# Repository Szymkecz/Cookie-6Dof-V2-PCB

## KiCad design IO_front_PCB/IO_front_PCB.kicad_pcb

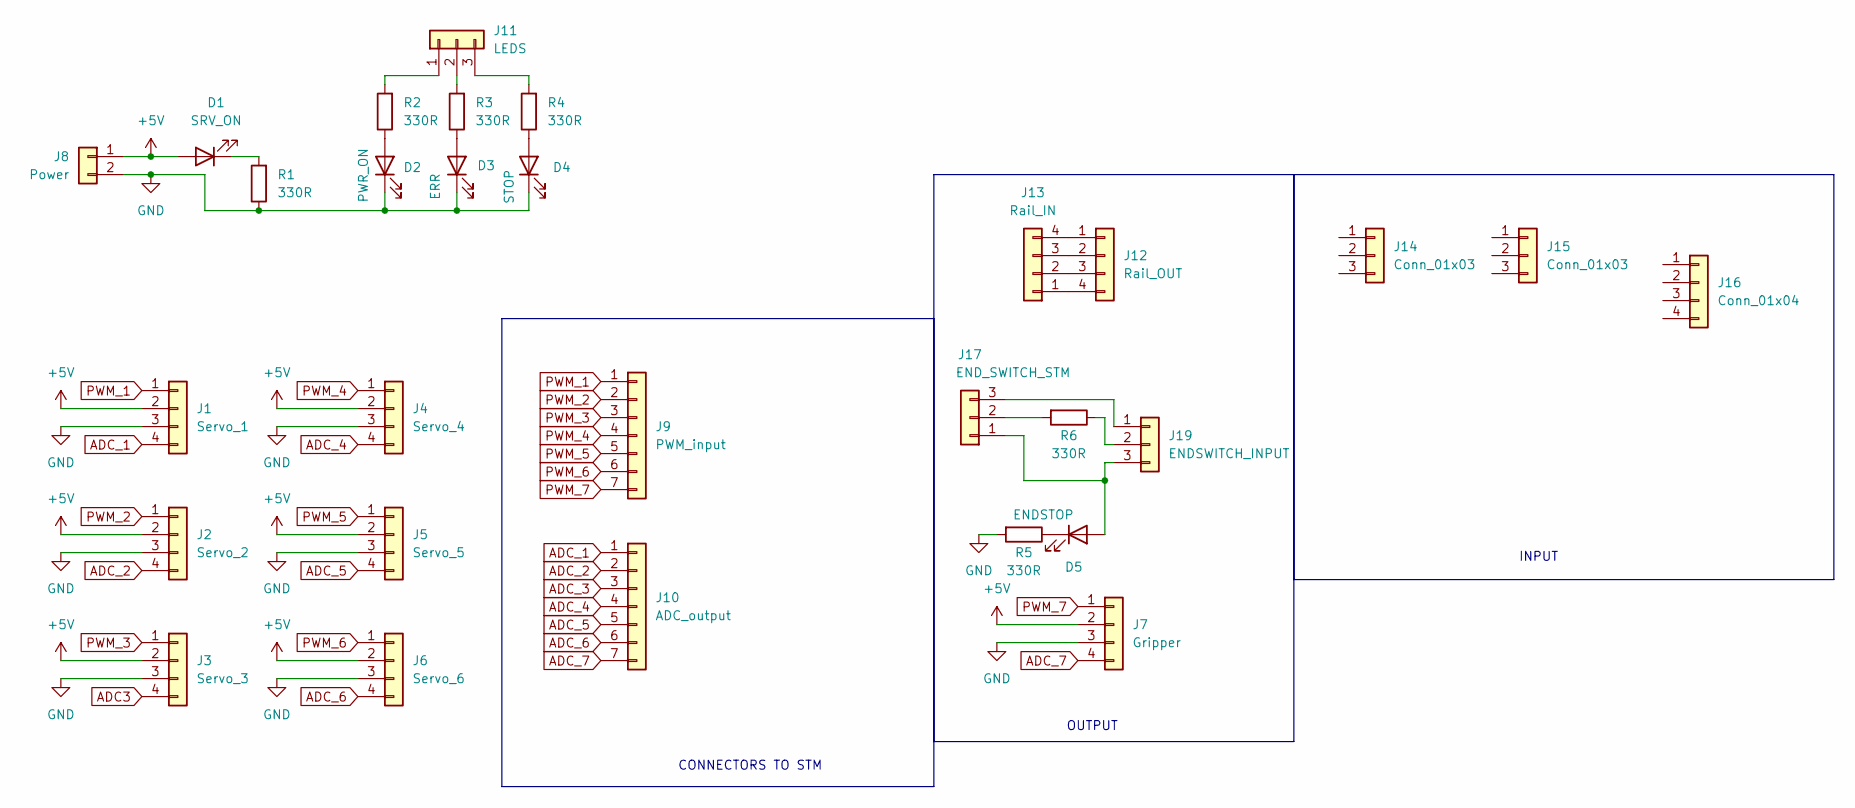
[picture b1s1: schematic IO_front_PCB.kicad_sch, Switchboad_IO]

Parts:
D1: SRV_ON; LED_D3.0mm
D2: PWR_ON; LED_D3.0mm
D3: ERR; LED_D3.0mm
D4: STOP; LED_D3.0mm
D5: ENDSTOP; LED_D3.0mm
J1: Servo_1; JST_XH_B4B-XH-A_1x04_P2.50mm_Vertical
J2: Servo_2; JST_XH_B4B-XH-A_1x04_P2.50mm_Vertical
J3: Servo_3; JST_XH_B4B-XH-A_1x04_P2.50mm_Vertical
J4: Servo_4; JST_XH_B4B-XH-A_1x04_P2.50mm_Vertical
J5: Servo_5; JST_XH_B4B-XH-A_1x04_P2.50mm_Vertical
J6: Servo_6; JST_XH_B4B-XH-A_1x04_P2.50mm_Vertical
J7: Gripper; JST_XH_B4B-XH-A_1x04_P2.50mm_Vertical
J8: Power; TerminalBlock_MaiXu_MX126-5.0-02P_1x02_P5.00mm
J9: PWM_input; PinHeader_1x07_P2.54mm_Vertical
J10: ADC_output; PinHeader_1x07_P2.54mm_Vertical
J11: LEDS; PinHeader_1x03_P2.54mm_Vertical
J12: Rail_OUT; JST_XH_B4B-XH-A_1x04_P2.50mm_Vertical
J13: Rail_IN; JST_XH_B4B-XH-A_1x04_P2.50mm_Vertical
J14, J15: Conn_01x03; JST_XH_B3B-XH-A_1x03_P2.50mm_Vertical
J16: Conn_01x04; JST_XH_B4B-XH-A_1x04_P2.50mm_Vertical
J17: END_SWITCH_STM; PinHeader_1x03_P2.54mm_Vertical
J19: ENDSWITCH_INPUT; JST_XH_B3B-XH-A_1x03_P2.50mm_Vertical
R1, R2, R3, R4, R5, R6: 330R; R_Axial_DIN0207_L6.3mm_D2.5mm_P7.62mm_Horizontal

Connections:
+5V: D1.2 (A), J1.2, J2.2, J3.2, J4.2, J5.2, J6.2, J7.2, J8.1
ADC3: J3.4
ADC_1: J1.4, J10.1
ADC_2: J2.4, J10.2
ADC_3: J10.3
ADC_4: J4.4, J10.4
ADC_5: J5.4, J10.5
ADC_6: J6.4, J10.6
ADC_7: J7.4, J10.7
GND: D2.1 (K), D3.1 (K), D4.1 (K), J1.3, J2.3, J3.3, J4.3, J5.3, J6.3, J7.3, J8.2, R1.1, R5.2
unnamed: D1.1 (K), R1.2
unnamed: D2.2 (A), R2.1
unnamed: D3.2 (A), R3.1
unnamed: D4.2 (A), R4.1
unnamed: D5.2 (A), J17.1, J19.3
unnamed: D5.1 (K), R5.1
unnamed: J11.1, R2.2
unnamed: J11.2, R3.2
unnamed: J11.3, R4.2
unnamed: J12.1, J13.4
unnamed: J12.2, J13.3
unnamed: J12.3, J13.2
unnamed: J12.4, J13.1
unnamed: J17.2, R6.2
unnamed: J17.3, J19.1
unnamed: J19.2, R6.1
PWM_1: J1.1, J9.1
PWM_2: J2.1, J9.2
PWM_3: J3.1, J9.3
PWM_4: J4.1, J9.4
PWM_5: J5.1, J9.5
PWM_6: J6.1, J9.6
PWM_7: J7.1, J9.7

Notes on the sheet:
INPUT
OUTPUT
CONNECTORS TO STM

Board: 2 copper layers, 29 parts (0 on the bottom side), 31 nets, no tracks yet.

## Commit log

2026-03-16 created schematic for v2 pcb
